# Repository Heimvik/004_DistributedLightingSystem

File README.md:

# Distributed LED System
## Overview
The Distributed LED System is a networked lighting project using ESP32 microcontrollers and individually addressable RGB LED strips. The system consists of a master node that processes signals and multiple slave nodes, each controlling a 1-meter LED strip. The system supports various lighting modes, including synchronization with music and spatial sound effects. When finished with the circuits to the second revision, the firmware for it will be developed in embedded C. Future progress will appear here shortly.

## Features

- **Centralized Control**: Master node coordinates LED patterns across all slave nodes.
- **Dynamic Lighting Modes**:
  - Static Colors
  - Dynamic Patterns
  - Music Synchronization
  - Spatial Sound Effects
- **Real-time Communication**: Efficiently communicates between master and slave nodes using MQTT/WebSockets.
- **User Interface**: Web-based or mobile app interface for control and configuration.

Status as of 09.10: Awaiting programmer for ESP32-WROOM32E, continuing prototyping with rpi.

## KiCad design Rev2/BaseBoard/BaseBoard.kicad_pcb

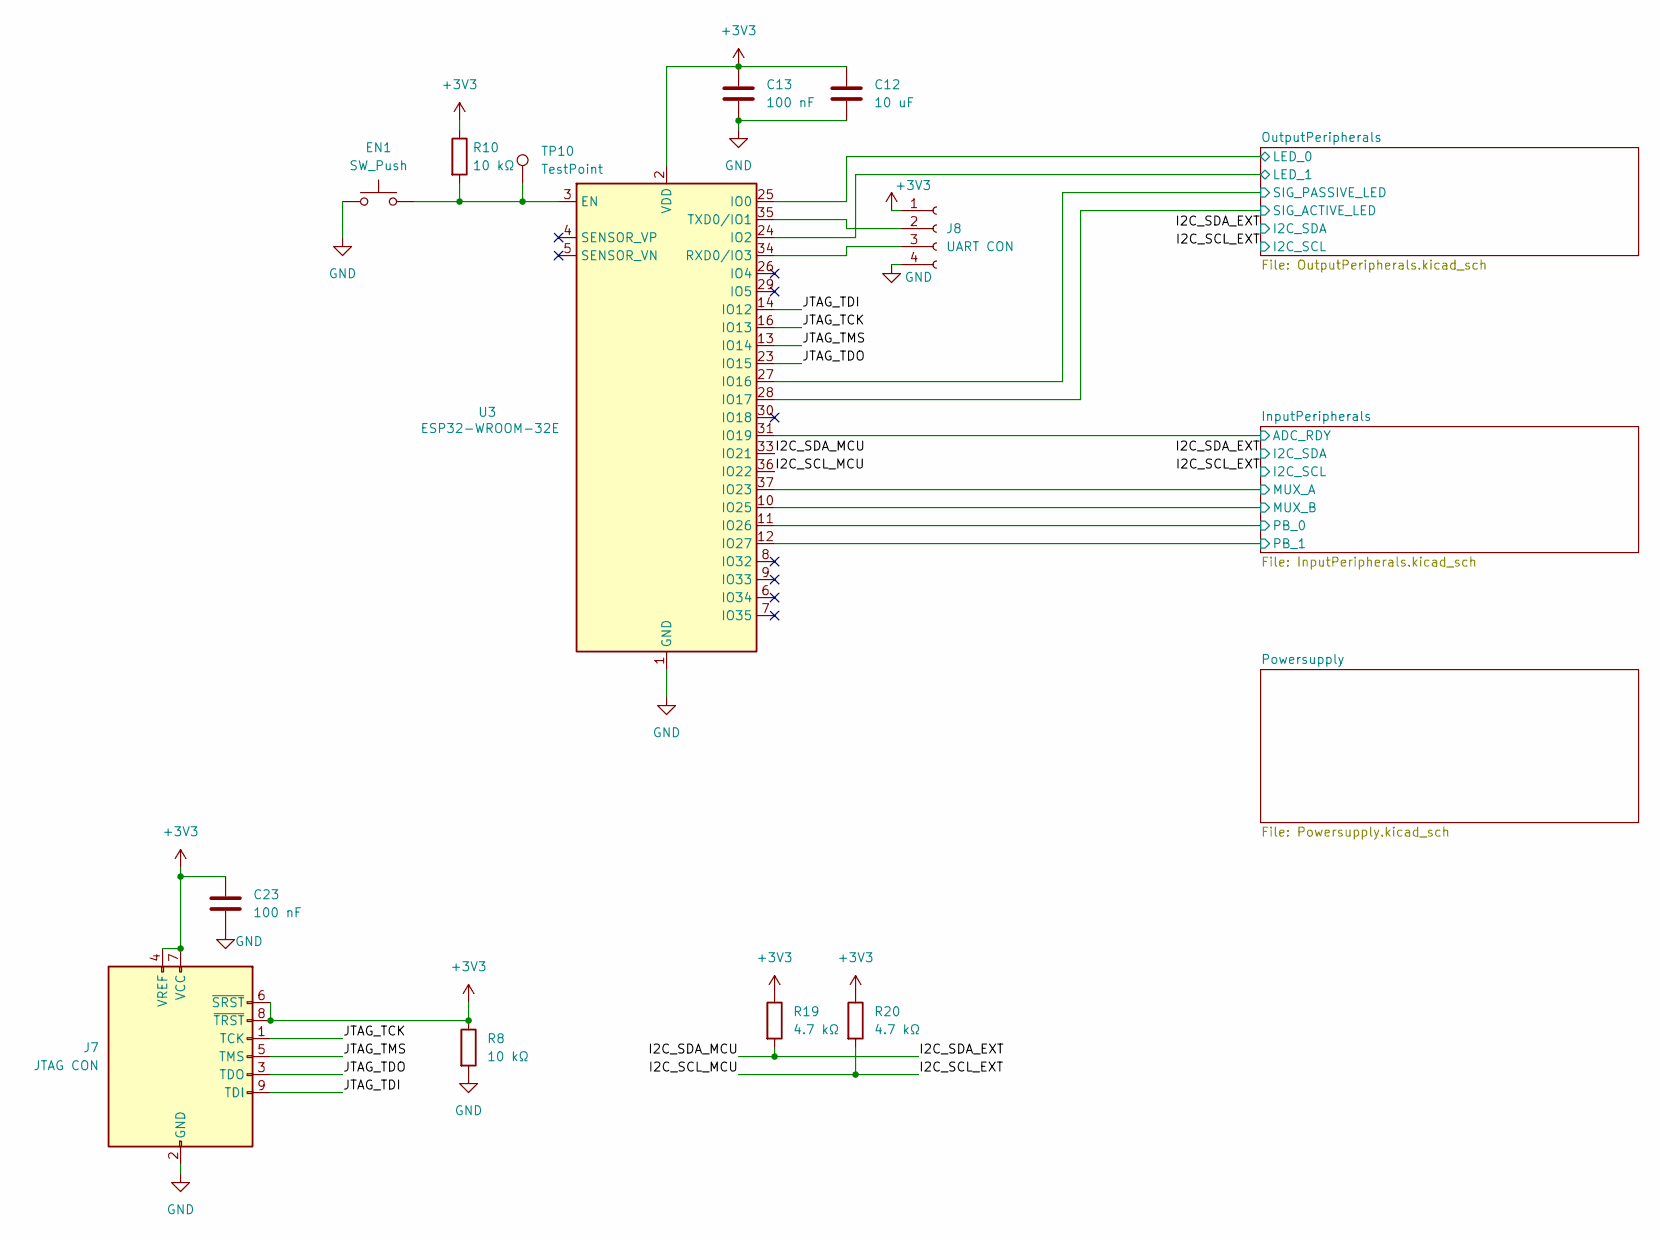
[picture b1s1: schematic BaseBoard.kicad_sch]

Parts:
C12: 10 uF; C_0805_2012Metric_Pad1.18x1.45mm_HandSolder
C13, C23: 100 nF; C_0805_2012Metric_Pad1.18x1.45mm_HandSolder
EN1: SW_Push; SW_Push_1P1T_NO_6x6mm_H9.5mm
J7: JTAG CON; IDC-Header_2x05_P2.54mm_Horizontal
J8: UART CON; PinSocket_1x04_P2.54mm_Horizontal
R8, R10: 10 kΩ; R_0805_2012Metric_Pad1.20x1.40mm_HandSolder
R19, R20: 4.7 kΩ; R_0805_2012Metric_Pad1.20x1.40mm_HandSolder
TP10: TestPoint; TestPoint_Pad_1.0x1.0mm
U3: ESP32-WROOM-32E; ESP32-WROOM-32D

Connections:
+3V3: C12.1, C13.1, C23.1, J7.4 (VREF), J7.6 (~SRST), J7.7 (VCC), J7.8 (~TRST), J8.1, R8.1, R10.1, R19.1, R20.1, U3.2 (VDD); also elsewhere on the board
/I2C_SCL_EXT: R20.2, U3.36 (IO22); also elsewhere on the board
/I2C_SDA_EXT: R19.2, U3.33 (IO21); also elsewhere on the board
/InputPeripherals/ADC_RDY: U3.31 (IO19); also elsewhere on the board
/InputPeripherals/MUX_A: U3.37 (IO23); also elsewhere on the board
/InputPeripherals/MUX_B: U3.10 (IO25); also elsewhere on the board
/InputPeripherals/PB_0: U3.11 (IO26); also elsewhere on the board
/InputPeripherals/PB_1: U3.12 (IO27); also elsewhere on the board
/JTAG_TCK: J7.1 (TCK), U3.16 (IO13)
/JTAG_TDI: J7.9 (TDI), U3.14 (IO12)
/JTAG_TDO: J7.3 (TDO), U3.23 (IO15)
/JTAG_TMS: J7.5 (TMS), U3.13 (IO14)
/OutputPeripherals/LED_0: U3.25 (IO0); also elsewhere on the board
/OutputPeripherals/LED_1: U3.24 (IO2); also elsewhere on the board
/OutputPeripherals/SIG_ACTIVE_LED: U3.28 (IO17); also elsewhere on the board
/OutputPeripherals/SIG_PASSIVE_LED: U3.27 (IO16); also elsewhere on the board
GND: C12.2, C13.2, C23.2, EN1.1, J7.2 (GND), J7.10 (GND), J8.4, R8.2, U3.1 (GND), U3.15 (GND), U3.38 (GND), U3.39 (GND); also elsewhere on the board
unnamed: J8.2, U3.35 (TXD0/IO1)
unnamed: J8.3, U3.34 (RXD0/IO3)
unnamed: EN1.2, R10.2, TP10.1, U3.3 (EN)

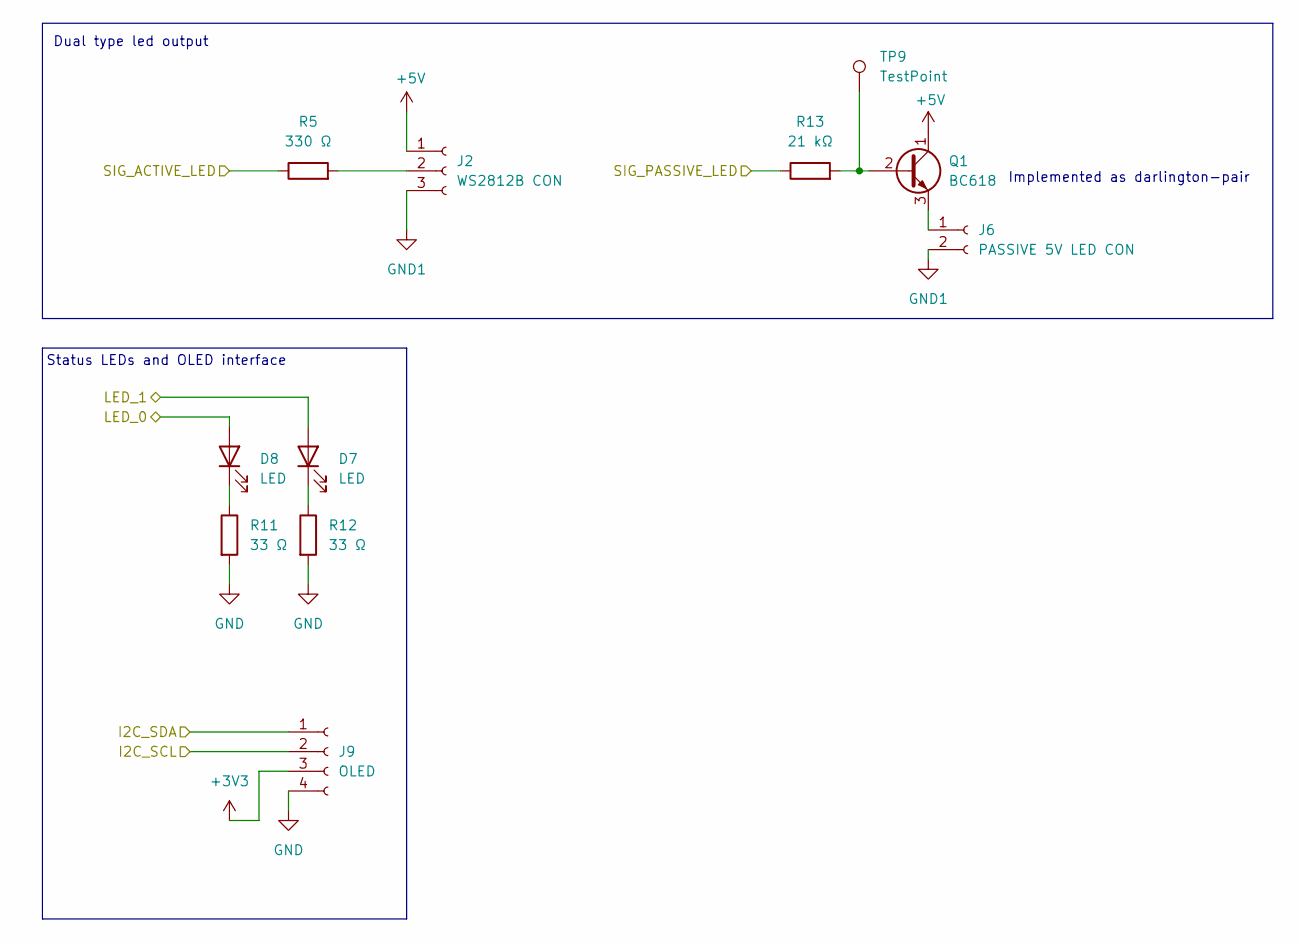
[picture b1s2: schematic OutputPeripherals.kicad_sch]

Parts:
D7, D8: LED; LED_0805_2012Metric_Pad1.15x1.40mm_HandSolder
J2: WS2812B CON; PinSocket_1x03_P2.54mm_Vertical
J6: PASSIVE 5V LED CON; PinSocket_1x02_P2.54mm_Vertical
J9: OLED; PinSocket_1x04_P2.54mm_Vertical
Q1: BC618; TO-92_Inline
R5: 330 Ω; R_0805_2012Metric_Pad1.20x1.40mm_HandSolder
R11, R12: 33 Ω; R_0805_2012Metric_Pad1.20x1.40mm_HandSolder
R13: 21 kΩ; R_0805_2012Metric_Pad1.20x1.40mm_HandSolder
TP9: TestPoint; TestPoint_Pad_1.0x1.0mm

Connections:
+3V3: J9.3; also elsewhere on the board
+5V: J2.1, Q1.1 (C); also elsewhere on the board
/I2C_SCL_EXT: J9.2; also elsewhere on the board
/I2C_SDA_EXT: J9.1; also elsewhere on the board
/OutputPeripherals/LED_0: D8.2 (A); also elsewhere on the board
/OutputPeripherals/LED_1: D7.2 (A); also elsewhere on the board
/OutputPeripherals/SIG_ACTIVE_LED: R5.1; also elsewhere on the board
/OutputPeripherals/SIG_PASSIVE_LED: R13.1; also elsewhere on the board
GND: J9.4, R11.2, R12.2; also elsewhere on the board
GND1: J2.3, J6.2; also elsewhere on the board
unnamed: D7.1 (K), R12.1
unnamed: D8.1 (K), R11.1
unnamed: J2.2, R5.2
unnamed: J6.1, Q1.3 (E)
unnamed: Q1.2 (B), R13.2, TP9.1

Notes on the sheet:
Dual type led output
Implemented as darlington-pair
Status LEDs and OLED interface

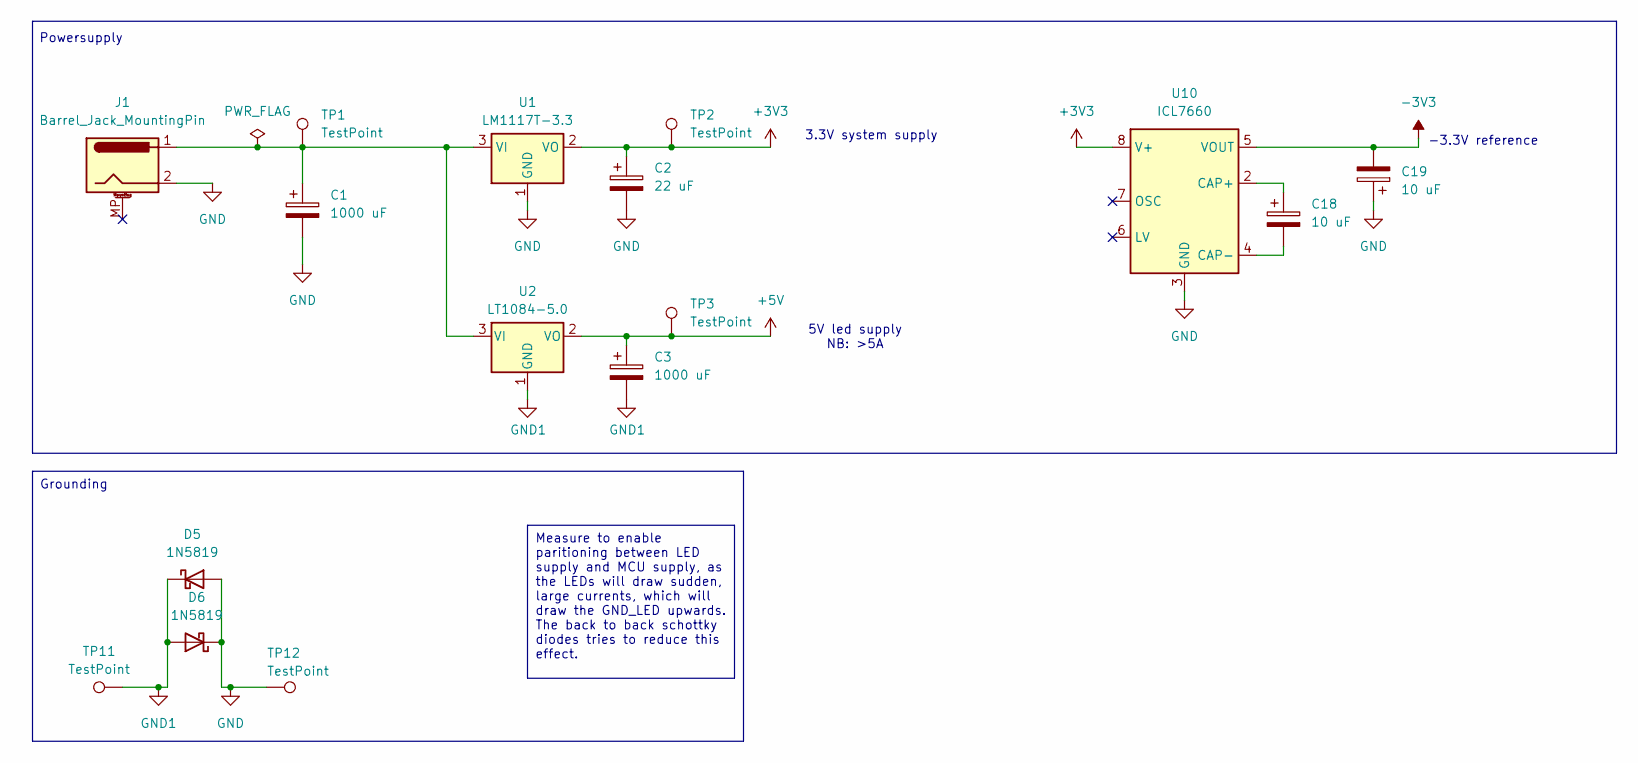
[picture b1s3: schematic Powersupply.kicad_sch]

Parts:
C1, C3: 1000 uF; CP_Radial_D10.0mm_P7.50mm
C2: 22 uF; CP_Radial_D6.3mm_P2.50mm
C18, C19: 10 uF; CP_Radial_D4.0mm_P2.00mm
D5, D6: 1N5819; D_DO-41_SOD81_P10.16mm_Horizontal
J1: Barrel_Jack_MountingPin; BarrelJack_Wuerth_694108106102_2.5x5.5mm
TP1, TP2, TP3, TP11, TP12: TestPoint; TestPoint_Pad_1.0x1.0mm
U1: LM1117T-3.3; TO-220-3_Vertical
U2: LT1084-5.0; TO-220-3_Vertical
U10: ICL7660

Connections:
+3V3: C2.1, TP2.1, U1.2 (VO), U10.8 (V+); also elsewhere on the board
+5V: C3.1, TP3.1, U2.2 (VO); also elsewhere on the board
-3V3: C19.2, U10.5 (VOUT); also elsewhere on the board
GND: C1.2, C2.2, C19.1, D5.2 (A), D6.1 (K), J1.2, TP12.1, U1.1 (GND), U10.3 (GND); also elsewhere on the board
GND1: C3.2, D5.1 (K), D6.2 (A), TP11.1, U2.1 (GND); also elsewhere on the board
unnamed: C1.1, J1.1, TP1.1, U1.3 (VI), U2.3 (VI)
unnamed: C18.1, U10.2 (CAP+)
unnamed: C18.2, U10.4 (CAP-)

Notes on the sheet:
Measure to enable paritioning between LED supply and MCU supply, as the LEDs will draw sudden, large currents, which will draw the GND_LED upwards. The back to back schottky diodes tries to reduce this effect.
3.3V system supply
Grounding
Powersupply
-3.3V reference
5V led supply NB: >5A

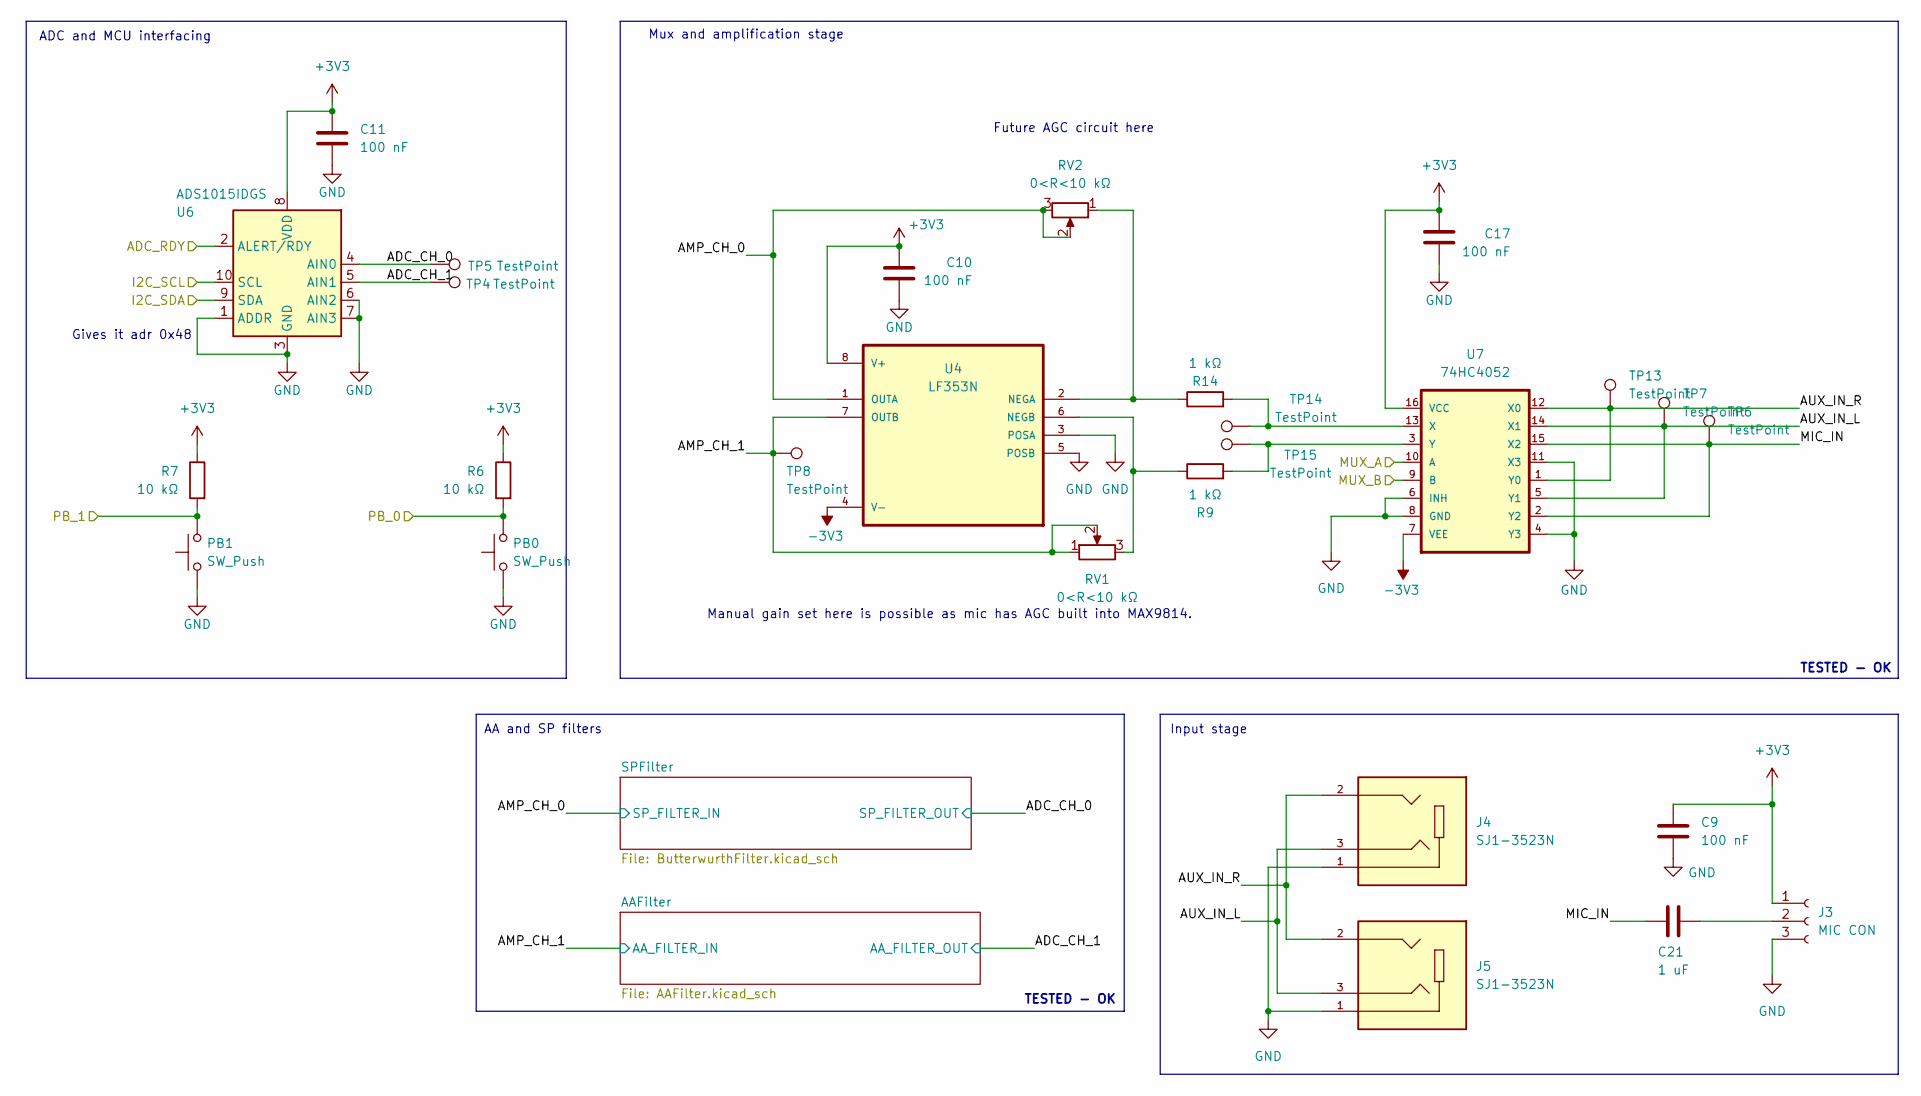
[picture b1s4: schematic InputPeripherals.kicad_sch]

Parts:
C9, C10, C11, C17: 100 nF; C_0805_2012Metric_Pad1.18x1.45mm_HandSolder
C21: 1 uF; C_0805_2012Metric_Pad1.18x1.45mm_HandSolder
J3: MIC CON; PinSocket_1x03_P2.54mm_Vertical
J4, J5: SJ1-3523N; CUI_SJ1-3523N; PARTREV 1.05
PB0, PB1: SW_Push; SW_Push_1P1T_NO_6x6mm_H9.5mm
R6, R7: 10 kΩ; R_0805_2012Metric_Pad1.20x1.40mm_HandSolder
R9, R14: 1 kΩ; R_0805_2012Metric_Pad1.20x1.40mm_HandSolder
RV1, RV2: 0<R<10 kΩ; PinSocket_1x03_P2.54mm_Vertical
TP4, TP5, TP6, TP7, TP8, TP13, TP14, TP15: TestPoint; TestPoint_Pad_1.0x1.0mm
U4: LF353N; LF353
U6: ADS1015IDGS; TSSOP-10_3x3mm_P0.5mm
U7: 74HC4052; MUX

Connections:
+3V3: C9.1, C10.1, C11.1, C17.1, J3.1, R6.1, R7.1, U4.8 (V+), U6.8 (VDD), U7.16 (VCC); also elsewhere on the board
-3V3: U4.4 (V-), U7.7 (VEE); also elsewhere on the board
/I2C_SCL_EXT: U6.10 (SCL); also elsewhere on the board
/I2C_SDA_EXT: U6.9 (SDA); also elsewhere on the board
/InputPeripherals/ADC_CH_0: TP5.1, U6.4 (AIN0); also elsewhere on the board
/InputPeripherals/ADC_CH_1: TP4.1, U6.5 (AIN1); also elsewhere on the board
/InputPeripherals/ADC_RDY: U6.2 (ALERT/RDY); also elsewhere on the board
/InputPeripherals/AMP_CH_0: RV2.2, RV2.3, U4.1 (OUTA); also elsewhere on the board
/InputPeripherals/AMP_CH_1: RV1.1, RV1.2, TP8.1, U4.7 (OUTB); also elsewhere on the board
/InputPeripherals/AUX_IN_L: J4.3, J5.3, TP7.1, U7.5 (Y1), U7.14 (X1)
/InputPeripherals/AUX_IN_R: J4.2, J5.2, TP13.1, U7.1 (Y0), U7.12 (X0)
/InputPeripherals/MIC_IN: C21.2, TP6.1, U7.2 (Y2), U7.15 (X2)
/InputPeripherals/MUX_A: U7.10 (A); also elsewhere on the board
/InputPeripherals/MUX_B: U7.9 (B); also elsewhere on the board
/InputPeripherals/PB_0: PB0.1, R6.2; also elsewhere on the board
/InputPeripherals/PB_1: PB1.1, R7.2; also elsewhere on the board
GND: C9.2, C10.2, C11.2, C17.2, J3.3, J4.1, J5.1, PB0.2, PB1.2, U4.3 (POSA), U4.5 (POSB), U6.1 (ADDR), U6.3 (GND), U6.6 (AIN2), U6.7 (AIN3), U7.4 (Y3), U7.6 (INH), U7.8 (GND), U7.11 (X3); also elsewhere on the board
unnamed: C21.1, J3.2
unnamed: R14.1, RV2.1, U4.2 (NEGA)
unnamed: R9.1, RV1.3, U4.6 (NEGB)
unnamed: R14.2, TP14.1, U7.13 (X)
unnamed: R9.2, TP15.1, U7.3 (Y)

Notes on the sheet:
AA and SP filters
TESTED - OK
Gives it adr 0x48
Future AGC circuit here
Input stage
Manual gain set here is possible as mic has AGC built into MAX9814.
Mux and amplification stage
ADC and MCU interfacing

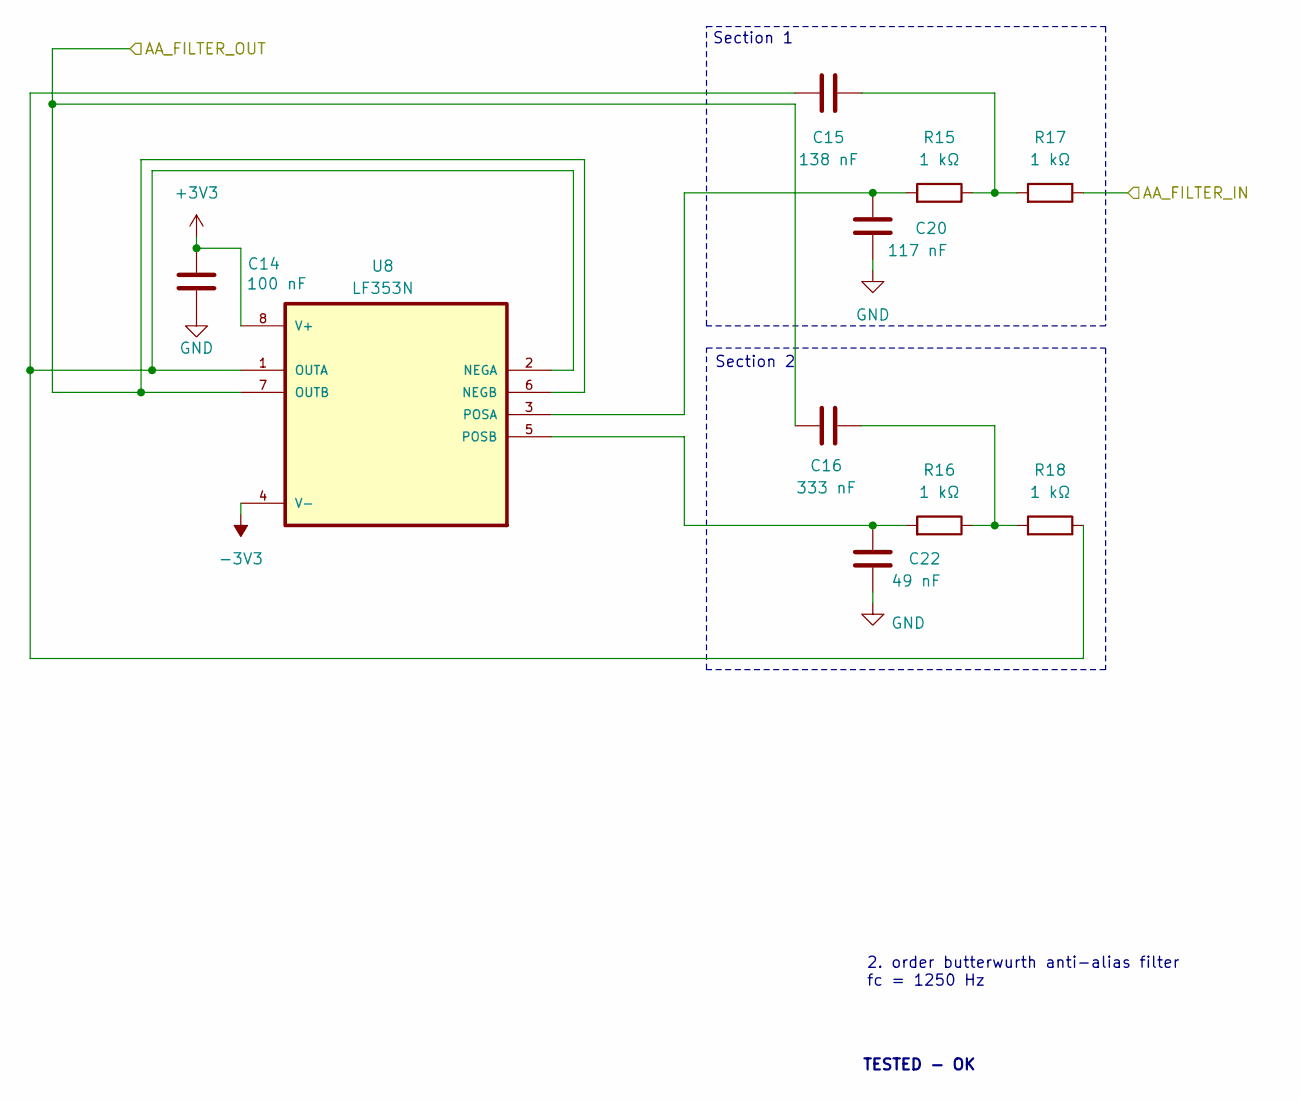
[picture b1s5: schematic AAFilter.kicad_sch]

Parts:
C14: 100 nF; C_0805_2012Metric_Pad1.18x1.45mm_HandSolder
C15: 138 nF; C_0805_2012Metric_Pad1.18x1.45mm_HandSolder
C16: 333 nF; C_0805_2012Metric_Pad1.18x1.45mm_HandSolder
C20: 117 nF; C_0805_2012Metric_Pad1.18x1.45mm_HandSolder
C22: 49 nF; C_0805_2012Metric_Pad1.18x1.45mm_HandSolder
R15, R16, R17, R18: 1 kΩ; R_0805_2012Metric_Pad1.20x1.40mm_HandSolder
U8: LF353N; LF353

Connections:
+3V3: C14.1, U8.8 (V+); also elsewhere on the board
-3V3: U8.4 (V-); also elsewhere on the board
/InputPeripherals/ADC_CH_1: C16.2, U8.6 (NEGB), U8.7 (OUTB); also elsewhere on the board
/InputPeripherals/AMP_CH_1: R17.1; also elsewhere on the board
GND: C14.2, C20.2, C22.2; also elsewhere on the board
unnamed: C15.1, R15.1, R17.2
unnamed: C16.1, R16.1, R18.2
unnamed: C15.2, R18.1, U8.1 (OUTA), U8.2 (NEGA)
unnamed: C20.1, R15.2, U8.3 (POSA)
unnamed: C22.1, R16.2, U8.5 (POSB)

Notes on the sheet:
TESTED - OK
2. order butterwurth anti-alias filter fc = 1250 Hz
Section 1
Section 2

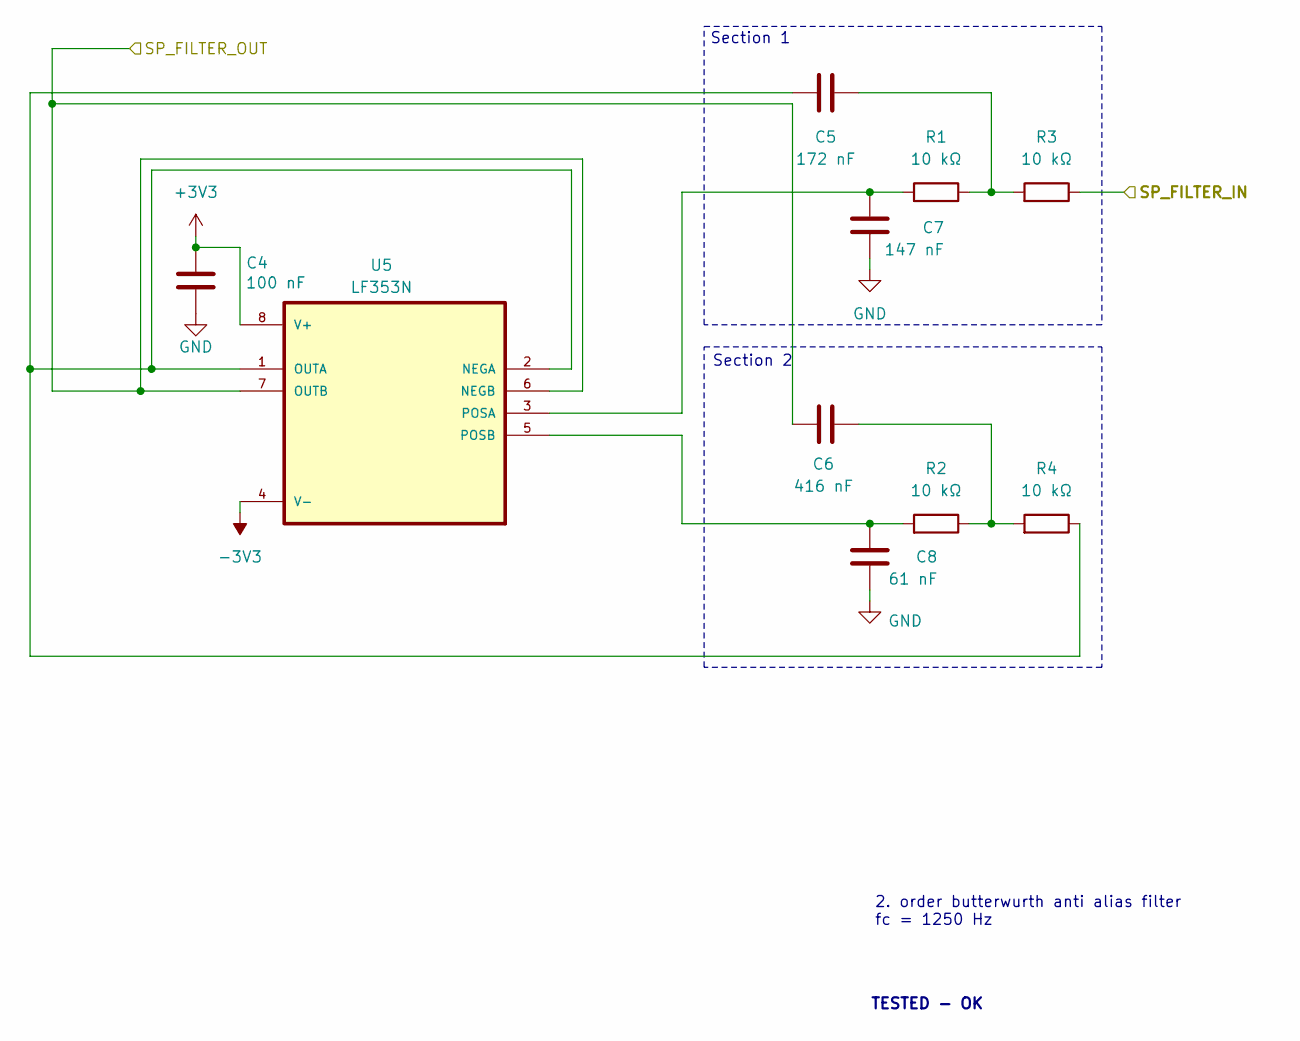
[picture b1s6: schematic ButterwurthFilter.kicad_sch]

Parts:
C4: 100 nF; C_0805_2012Metric_Pad1.18x1.45mm_HandSolder
C5: 172 nF; C_0805_2012Metric_Pad1.18x1.45mm_HandSolder
C6: 416 nF; C_0805_2012Metric_Pad1.18x1.45mm_HandSolder
C7: 147 nF; C_0805_2012Metric_Pad1.18x1.45mm_HandSolder
C8: 61 nF; C_0805_2012Metric_Pad1.18x1.45mm_HandSolder
R1, R2, R3, R4: 10 kΩ; R_0805_2012Metric_Pad1.20x1.40mm_HandSolder
U5: LF353N; LF353

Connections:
+3V3: C4.1, U5.8 (V+); also elsewhere on the board
-3V3: U5.4 (V-); also elsewhere on the board
/InputPeripherals/ADC_CH_0: C6.2, U5.6 (NEGB), U5.7 (OUTB); also elsewhere on the board
/InputPeripherals/AMP_CH_0: R3.1; also elsewhere on the board
GND: C4.2, C7.2, C8.2; also elsewhere on the board
unnamed: C5.1, R1.1, R3.2
unnamed: C6.1, R2.1, R4.2
unnamed: C5.2, R4.1, U5.1 (OUTA), U5.2 (NEGA)
unnamed: C7.1, R1.2, U5.3 (POSA)
unnamed: C8.1, R2.2, U5.5 (POSB)

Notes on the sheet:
TESTED - OK
2. order butterwurth anti alias filter fc = 1250 Hz
Section 2
Section 1

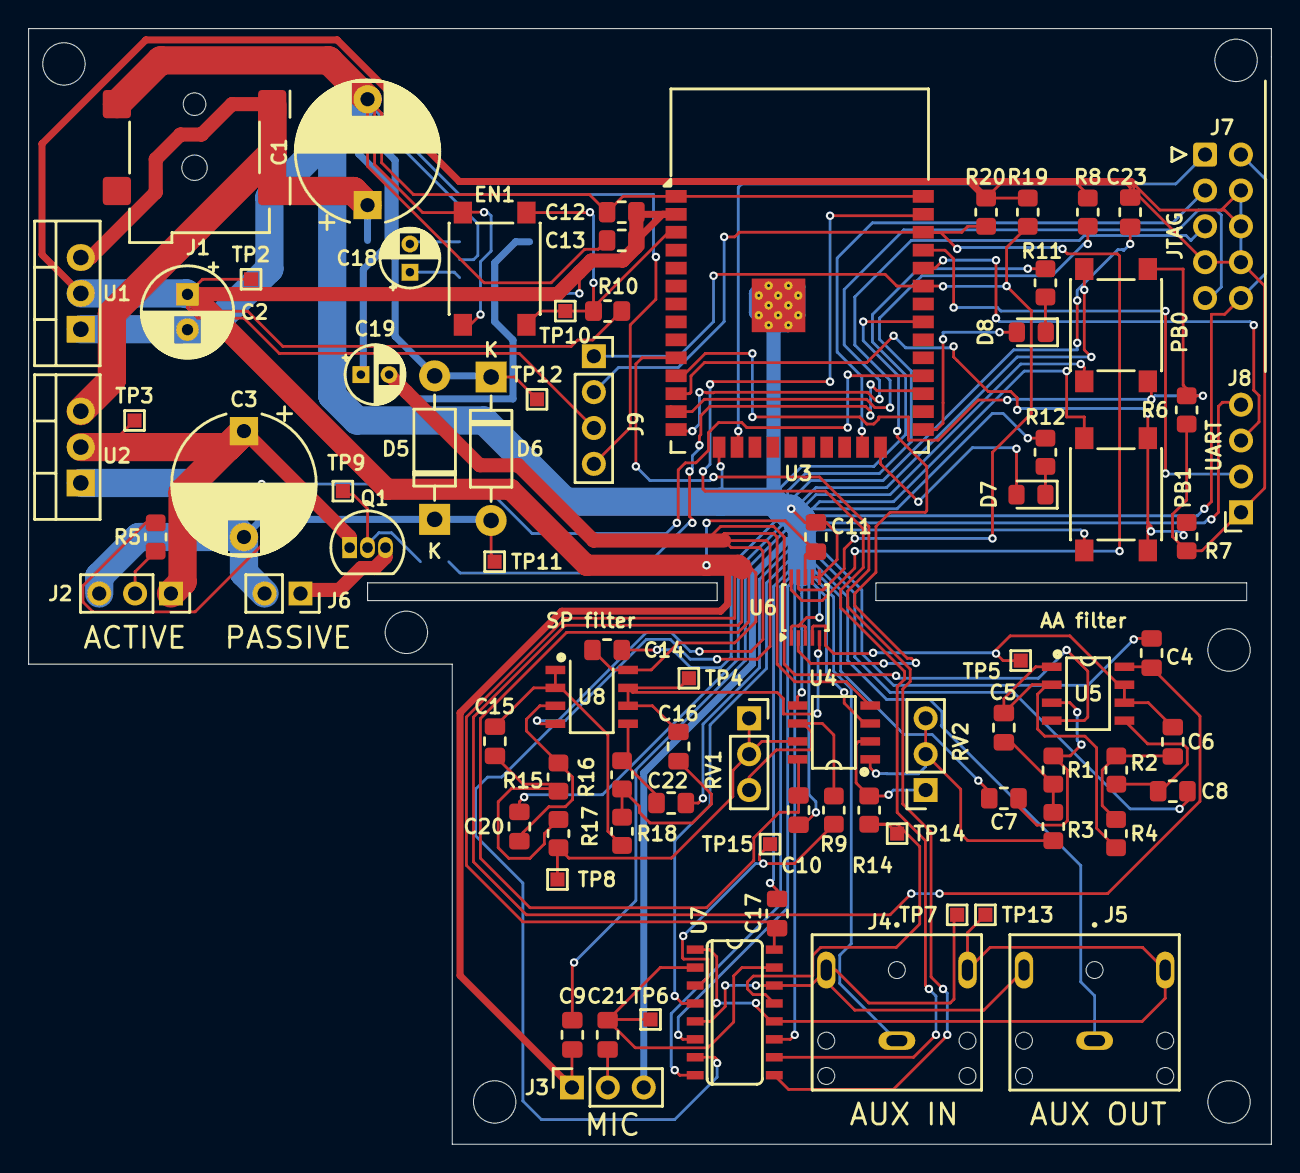
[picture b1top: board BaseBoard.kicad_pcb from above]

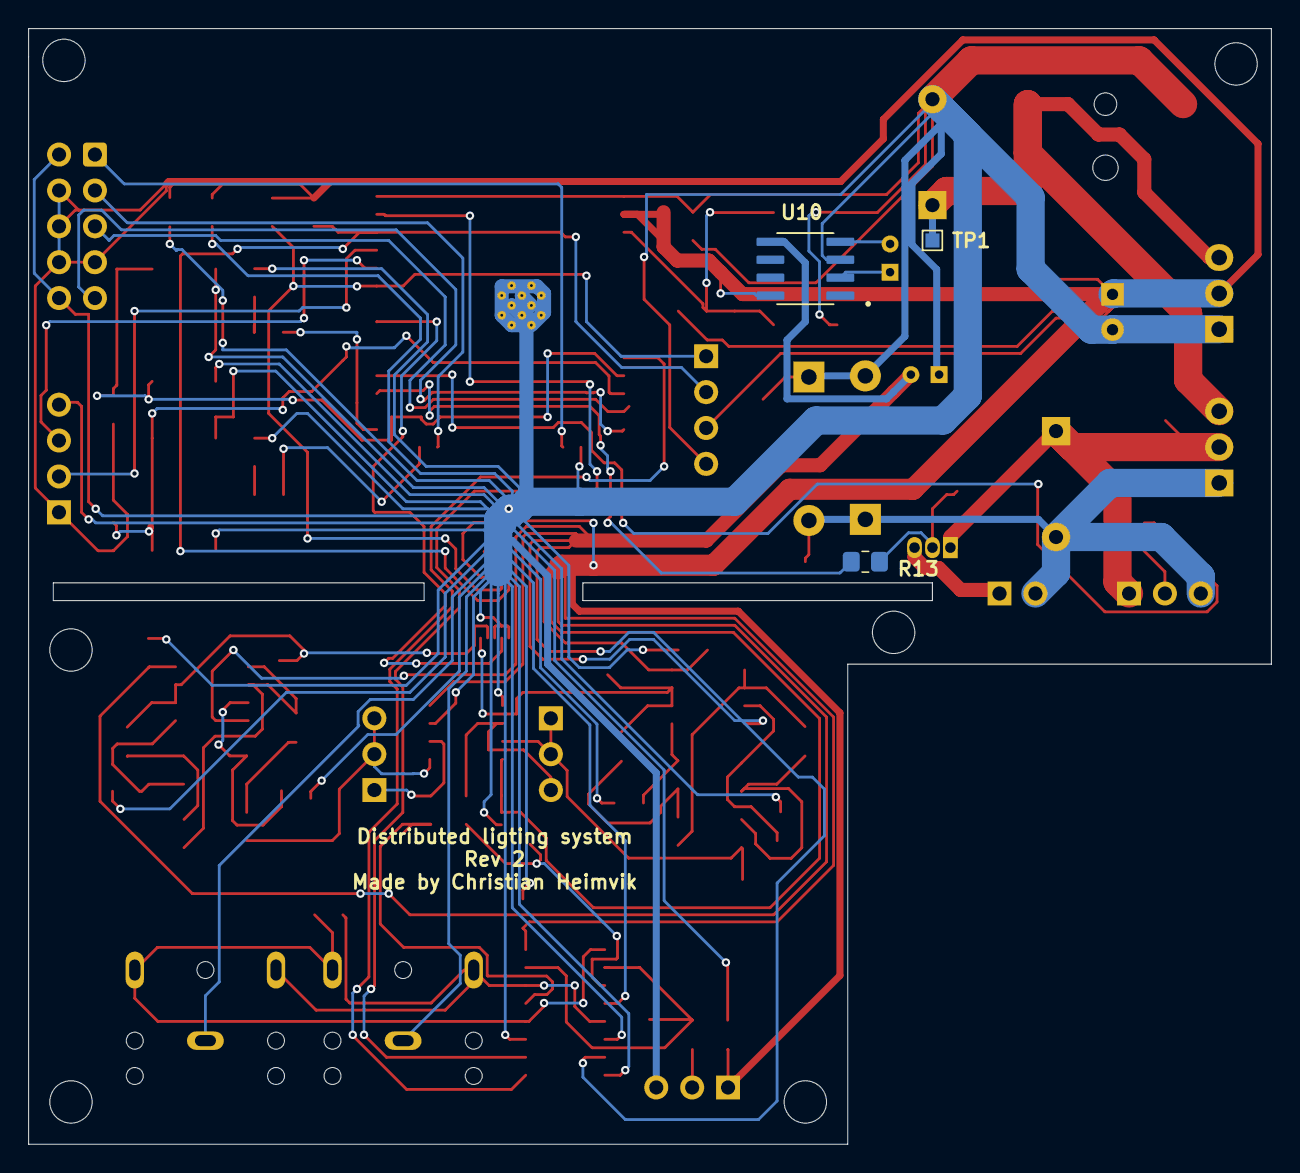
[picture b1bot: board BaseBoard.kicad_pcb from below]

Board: 2 copper layers, 88.0 x 79.0 mm, 86 parts (3 on the bottom side), 53 nets.

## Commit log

2024-09-07 Added ADC an peripherals
2024-09-07 Added Testpoints, UART and JTAG
2024-09-10 Finished placement, routing remains
2024-09-11 Finished rev 2
2024-09-11 Images and BOM
2024-10-09 Added structure
2024-10-09 Updated Doc
2024-10-09 Added setup bash script
2024-10-09 Started on c wrapper for GPU_FFT
2024-10-09 spotifyDriver untested, but finished
2024-10-09 Added config files
2024-10-09 Removed non-supported GPU usage, CPU (numpy) fft instead
2024-10-09 Spotify client working
2024-10-09 Working on capturing device
2024-10-09 Added div
2024-10-10 Error detection
2024-10-13 Using sounddevice rather than pyaudio
2024-10-13 More dsp vis
2024-10-13 Performance parameters for fft
2024-10-13 Added more fft performance counters
2024-10-14 Added ledstrip logic
2024-10-14 Added all
